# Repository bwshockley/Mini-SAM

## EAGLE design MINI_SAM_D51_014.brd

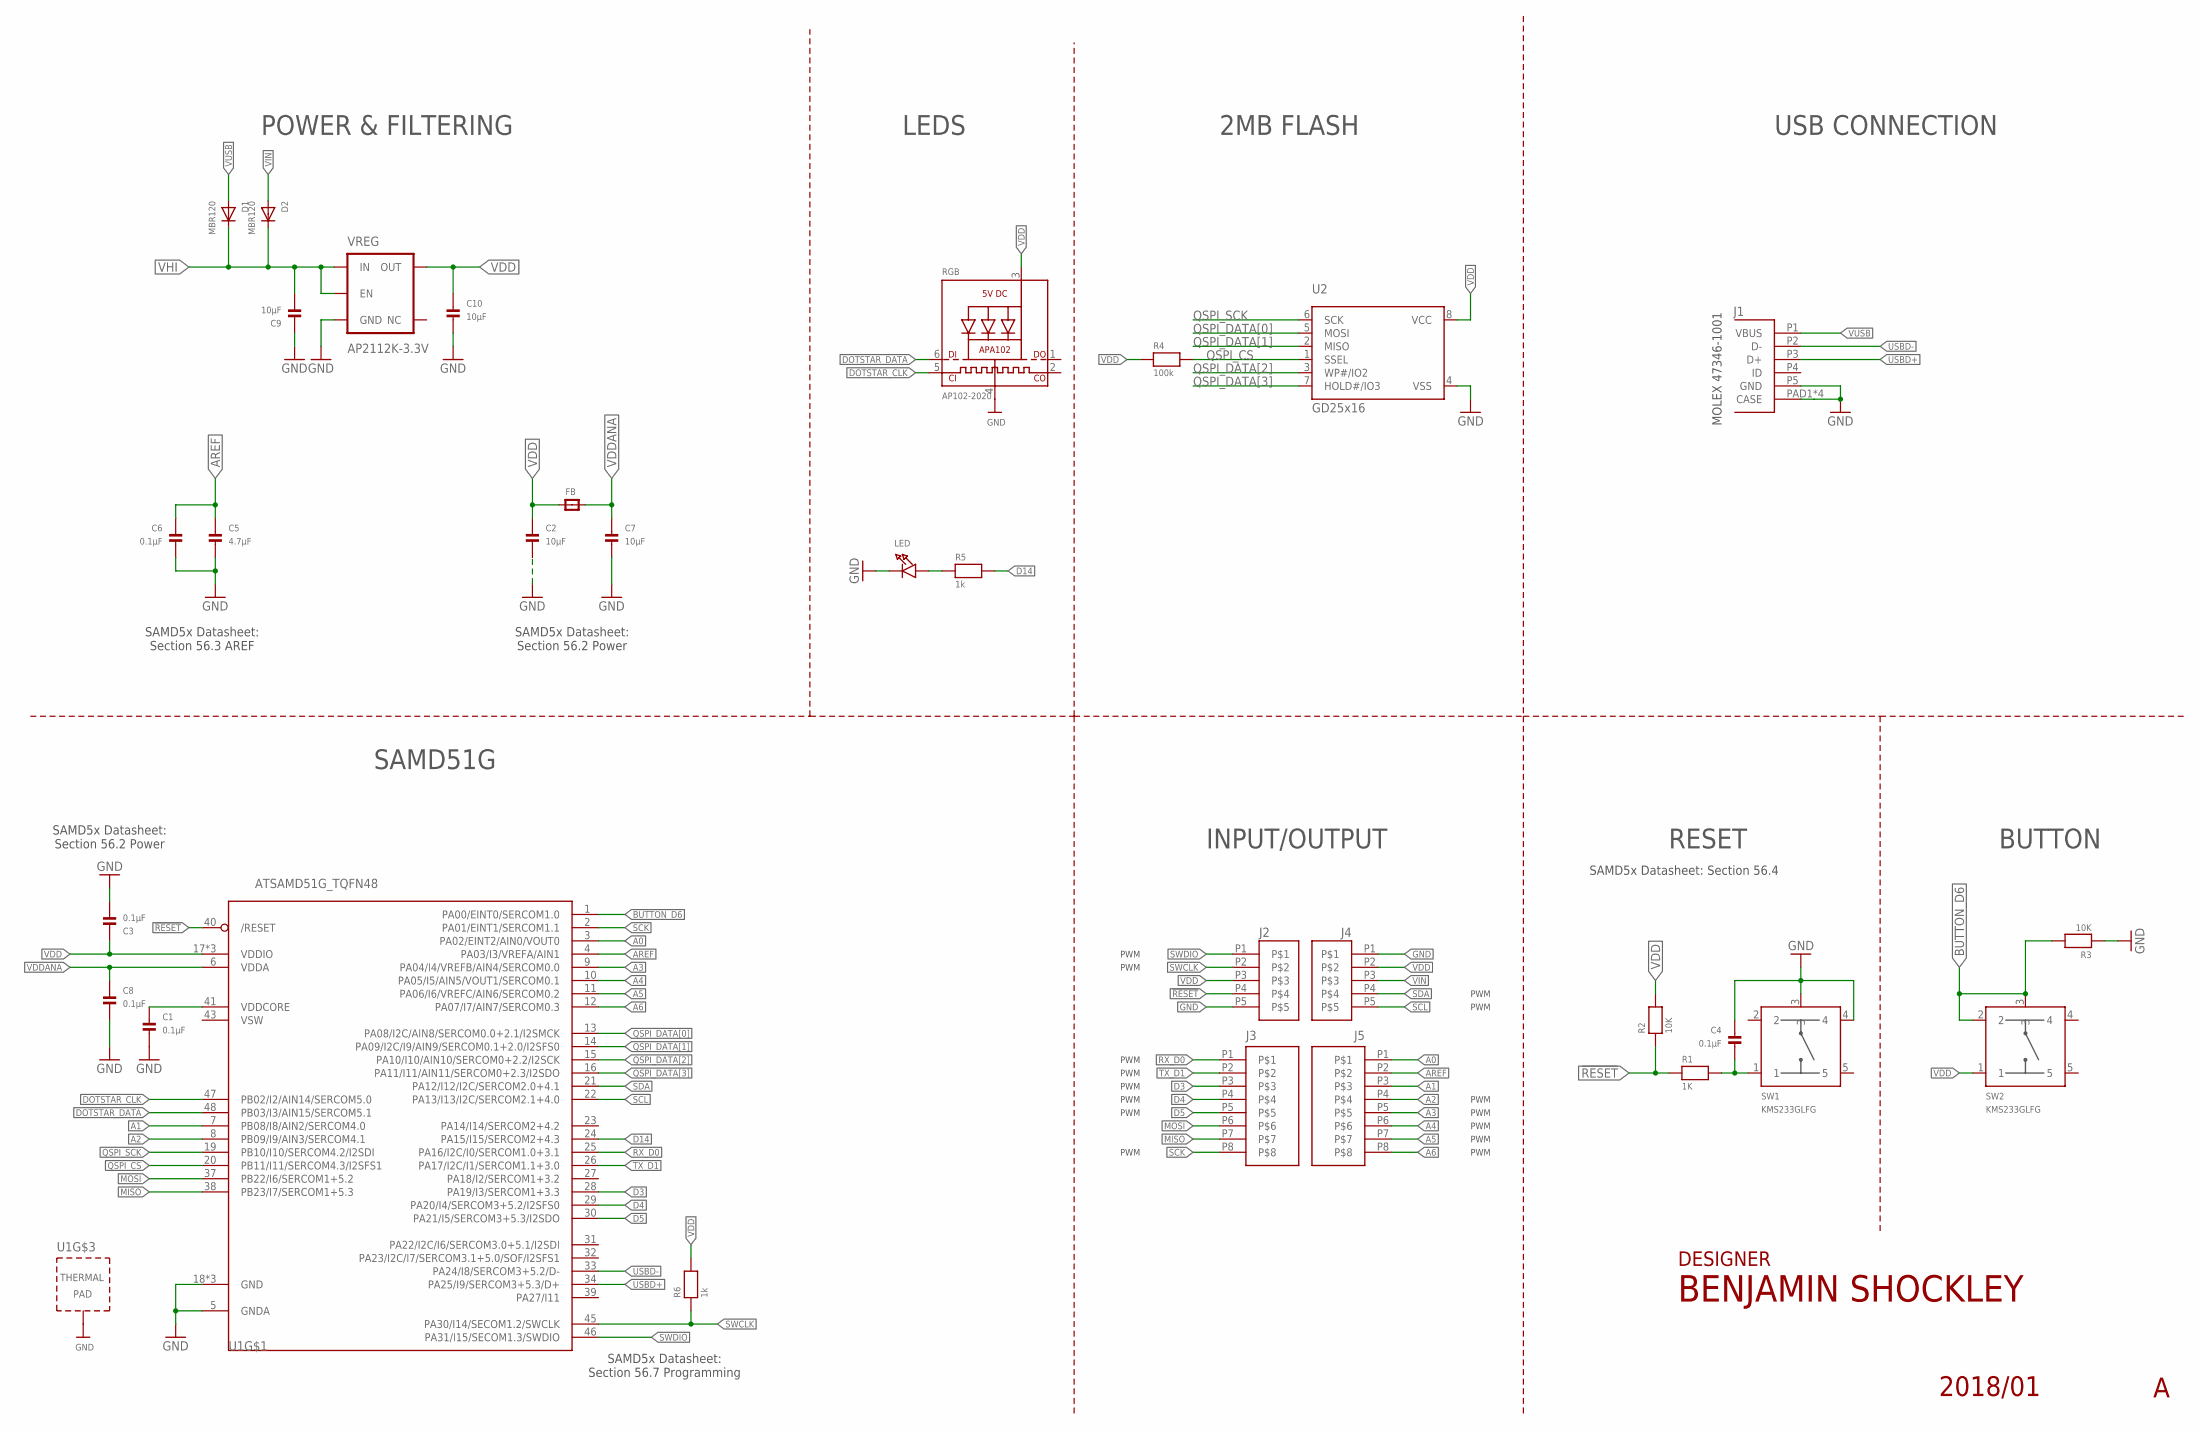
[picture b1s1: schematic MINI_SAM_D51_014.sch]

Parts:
C1, C3, C4, C6, C8: 0.1µF; _0603MP
C2, C7, C9, C10: 10µF; _0603MP
C5: 4.7µF; _0603MP
D1, D2: MBR120; SOD-123FL
FB: FERRITE_0603MP; _0603MP
J1: MOLEX_47346-100147346; MOLEX_47346-1001
J2, J4: 1X5_HEADER_1.27MMCAST; 1X5_HEADER_1.27MM_CASTELLATED
J3, J5: 1X8_HEADER_1.27MMCAST; 1X8_HEADER_1.27MM_CASTELLATED
LED: LED0805_NOOUTLINE; CHIPLED_0805_NOOUTLINE
R1: 1K; _0603MP
R2, R3: 10K; _0603MP
R4: 100k; _0603MP
R5, R6: 1k; _0603MP
RGB: AP102-2020; APA102_2020
SW1, SW2: KMS233GLFG; KMS_SWITCH
U1: ATSAMD51G_TQFN48; TQFN48_7MM
U2: GD25x16; USON8
VREG: AP2112K-3.3V; SOT23-5

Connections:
!RESET: J2.P4, R1.1, R2.1, U1.40 (/RESET)
A0: J5.P1, U1.3 (PA02/EINT2/AIN0/VOUT0)
A1: J5.P3, U1.7 (PB08/I8/AIN2/SERCOM4.0)
A2: J5.P4, U1.8 (PB09/I9/AIN3/SERCOM4.1)
A3: J5.P5, U1.9 (PA04/I4/VREFB/AIN4/SERCOM0.0)
A4: J5.P6, U1.10 (PA05/I5/AIN5/VOUT1/SERCOM0.1)
A5: J5.P7, U1.11 (PA06/I6/VREFC/AIN6/SERCOM0.2)
A6: J5.P8, U1.12 (PA07/I7/AIN7/SERCOM0.3)
AREF: C5.1, C6.1, J5.P2, U1.4 (PA03/I3/VREFA/AIN1)
BUTTON_D6: R3.2, SW2.2, SW2.3, U1.1 (PA00/EINT0/SERCOM1.0)
D3: J3.P3, U1.28 (PA19/I3/SERCOM1+3.3)
D4: J3.P4, U1.29 (PA20/I4/SERCOM3+5.2/I2SFS0)
D5: J3.P5, U1.30 (PA21/I5/SERCOM3+5.3/I2SDO)
D14: R5.2, U1.24 (PA15/I15/SERCOM2+4.3)
DOTSTAR_CLK: RGB.5 (CKI), U1.47 (PB02/I2/AIN14/SERCOM5.0)
DOTSTAR_DATA: RGB.6 (DI), U1.48 (PB03/I3/AIN15/SERCOM5.1)
GND: C1.2, C2.2, C3.2, C4.1, C5.2, C6.2, C7.2, C8.2, C9.1, C10.2, J1.P5 (GND), J1.PAD1 (CASE), J1.PAD2 (CASE), J1.PAD3 (CASE), J1.PAD4 (CASE), J2.P5, J4.P1, LED.C, R3.1, RGB.4 (GND), SW1.3, SW1.4, U1.5 (GNDA), U1.18 (GND), U1.35 (GND), U1.42 (GND), U1.THERMAL (TP), U2.4 (VSS), VREG.2 (GND)
MISO: J3.P7, U1.38 (PB23/I7/SERCOM1+5.3)
MOSI: J3.P6, U1.37 (PB22/I6/SERCOM1+5.2)
unnamed: LED.A, R5.1
unnamed: C4.2, R1.2, SW1.1
unnamed: C1.1, U1.41 (VDDCORE)
QSPI_CS: R4.2, U1.20 (PB11/I11/SERCOM4.3/I2SFS1), U2.1 (SSEL)
QSPI_DATA[0]: U1.13 (PA08/I2C/AIN8/SERCOM0.0+2.1/I2SMCK), U2.5 (MOSI)
QSPI_DATA[1]: U1.14 (PA09/I2C/I9/AIN9/SERCOM0.1+2.0/I2SFS0), U2.2 (MISO)
QSPI_DATA[2]: U1.15 (PA10/I10/AIN10/SERCOM0+2.2/I2SCK), U2.3 (WP#/IO2)
QSPI_DATA[3]: U1.16 (PA11/I11/AIN11/SERCOM0+2.3/I2SDO), U2.7 (HOLD#/IO3)
QSPI_SCK: U1.19 (PB10/I10/SERCOM4.2/I2SDI), U2.6 (SCK)
RX_D0: J3.P1, U1.25 (PA16/I2C/I0/SERCOM1.0+3.1)
SCK: J3.P8, U1.2 (PA01/EINT1/SERCOM1.1)
SCL: J4.P5, U1.22 (PA13/I13/I2C/SERCOM2.1+4.0)
SDA: J4.P4, U1.21 (PA12/I12/I2C/SERCOM2.0+4.1)
SWCLK: J2.P2, R6.1, U1.45 (PA30/I14/SECOM1.2/SWCLK)
SWDIO: J2.P1, U1.46 (PA31/I15/SECOM1.3/SWDIO)
TX_D1: J3.P2, U1.26 (PA17/I2C/I1/SERCOM1.1+3.0)
USBD+: J1.P3 (D+), U1.34 (PA25/I9/SERCOM3+5.3/D+)
USBD-: J1.P2 (D-), U1.33 (PA24/I8/SERCOM3+5.2/D-)
VDD: C2.1, C3.1, C10.1, FB.1, J2.P3, J4.P2, R2.2, R4.1, R6.2, RGB.3 (VDD), SW2.1, U1.17 (VDDIO), U1.36 (VDDIO), U1.44 (VDDIO), U2.8 (VCC), VREG.5 (OUT)
VDDANA: C7.1, C8.1, FB.2, U1.6 (VDDA)
VHI: C9.2, D1.C, D2.C, VREG.1 (IN), VREG.3 (EN)
VIN: D2.A, J4.P3
VSW: U1.43 (VSW)
VUSB: D1.A, J1.P1 (VBUS)

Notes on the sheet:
INPUT/OUTPUT
RESET
POWER & FILTERING
SAMD51G
LEDS
USB CONNECTION
MOLEX 47346-1001
BUTTON
DESIGNER
SAMD5x Datasheet: Section 56.4
2MB FLASH
SAMD5x Datasheet: Section 56.3 AREF
SAMD5x Datasheet: Section 56.2 Power
SAMD5x Datasheet: Section 56.7 Programming
PWM

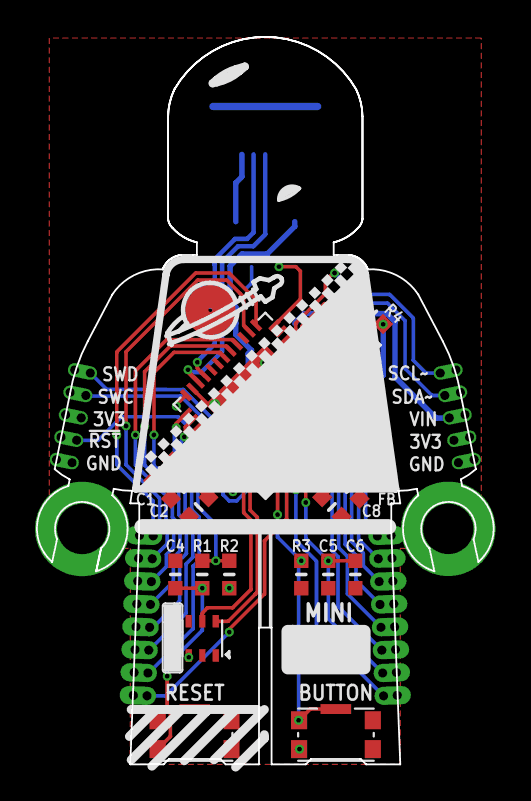
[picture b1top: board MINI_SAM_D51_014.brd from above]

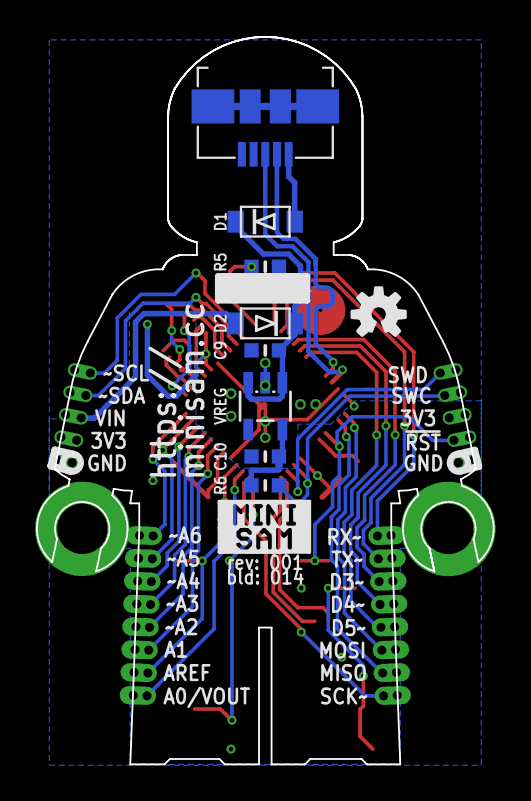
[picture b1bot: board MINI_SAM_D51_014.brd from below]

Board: 2 copper layers, 25.4 x 40.4 mm, 32 parts (10 on the bottom side), 42 nets.

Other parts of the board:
U$3: OSHW-LOGO-S

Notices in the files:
parts and their libraries:
microbuilder: This work is placed in the public domain, and may be freely used for commercial and non-commercial work with the following conditions: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
SparkFun-Aesthetics: Licensing: Creative Commons ShareAlike 4.0 International - https://creativecommons.org/licenses/by-sa/4.0
